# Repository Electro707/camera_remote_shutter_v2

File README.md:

# P1010 - Camera Remote Shutter Project V2
#### Rev 2

This is an open-source camera remote shutter.

This was the second revision of the [original project](https://github.com/Electro707/camera_remote_shutter), but is now treated as a seperate project due to scope creep.

Currently working on Rev 2, which is smaller and fixed some issues with V1

# Directory Structure
- `CAD`: FreeCAD enclosure and models
    - C1013: Bottom half of enclosure
    - C1014: Top half of enclosure
- `Firmware`: Firmware. Currently contains only test firmware
- `PCB`: KiCAD PCB Files
    - E1011: PCB
- `Release`: Locked in "released" files, such as Schematics, Gerbers, etc
- `SimTest`: A simulation I did in KiCAD for the trans-impedance amplifier

## Erratas
All hardware erratas and potential work-arounds are documented in [ERRATA.md](ERRATA.md)

## Firmware
WIP, currently only test firmware exists

### Setup
This project uses [stm32-cmake](https://github.com/ObKo/stm32-cmake) in the build process, so you must set it up and change the `CMAKE_TOOLCHAIN_FILE` variable in each firmware's CMAKE file. You must also download [STM32G0's MCU Package](https://github.com/STMicroelectronics/STM32CubeG0) and set the `STM32_CUBE_G0_PATH` variable to the download location.
Optionally if you have stm32cubeide installed, setup `STM32_TOOLCHAIN_PATH` in the CMAKE file, or remove it

### Compiling
To build any of the test or main applications, go into that directory and run the following:
```bash
mkdir -p build
cd build
cmake ../
make
```

### Programming
To upload the program, run the following stlink command
```bash
st-flash write <file_to_flash>.bin 0x08000000
```

Where the <file_to_flash> is the bin file inside of the build folder. `0x08000000` is the starting flash address for the STM32G0 family.

## KiCAD 3D Models
The 3D models for some components in the directory `PCB/3d_model/` are not included due to licensing reasons. You can grab the step files yourself and put it in that directory from the manufacturer. The models are
- CUI_DEVICES_SJ-2509N.step
- 615006138421_Download_STP_615006138421_rev1.stp
- c-1-1478035-0-b-3d.stp
- pec12r-4025f-n0024.stp

# License
This project is licensed under GPLv3. See [LICENSE.md](LICENSE.md) for details.

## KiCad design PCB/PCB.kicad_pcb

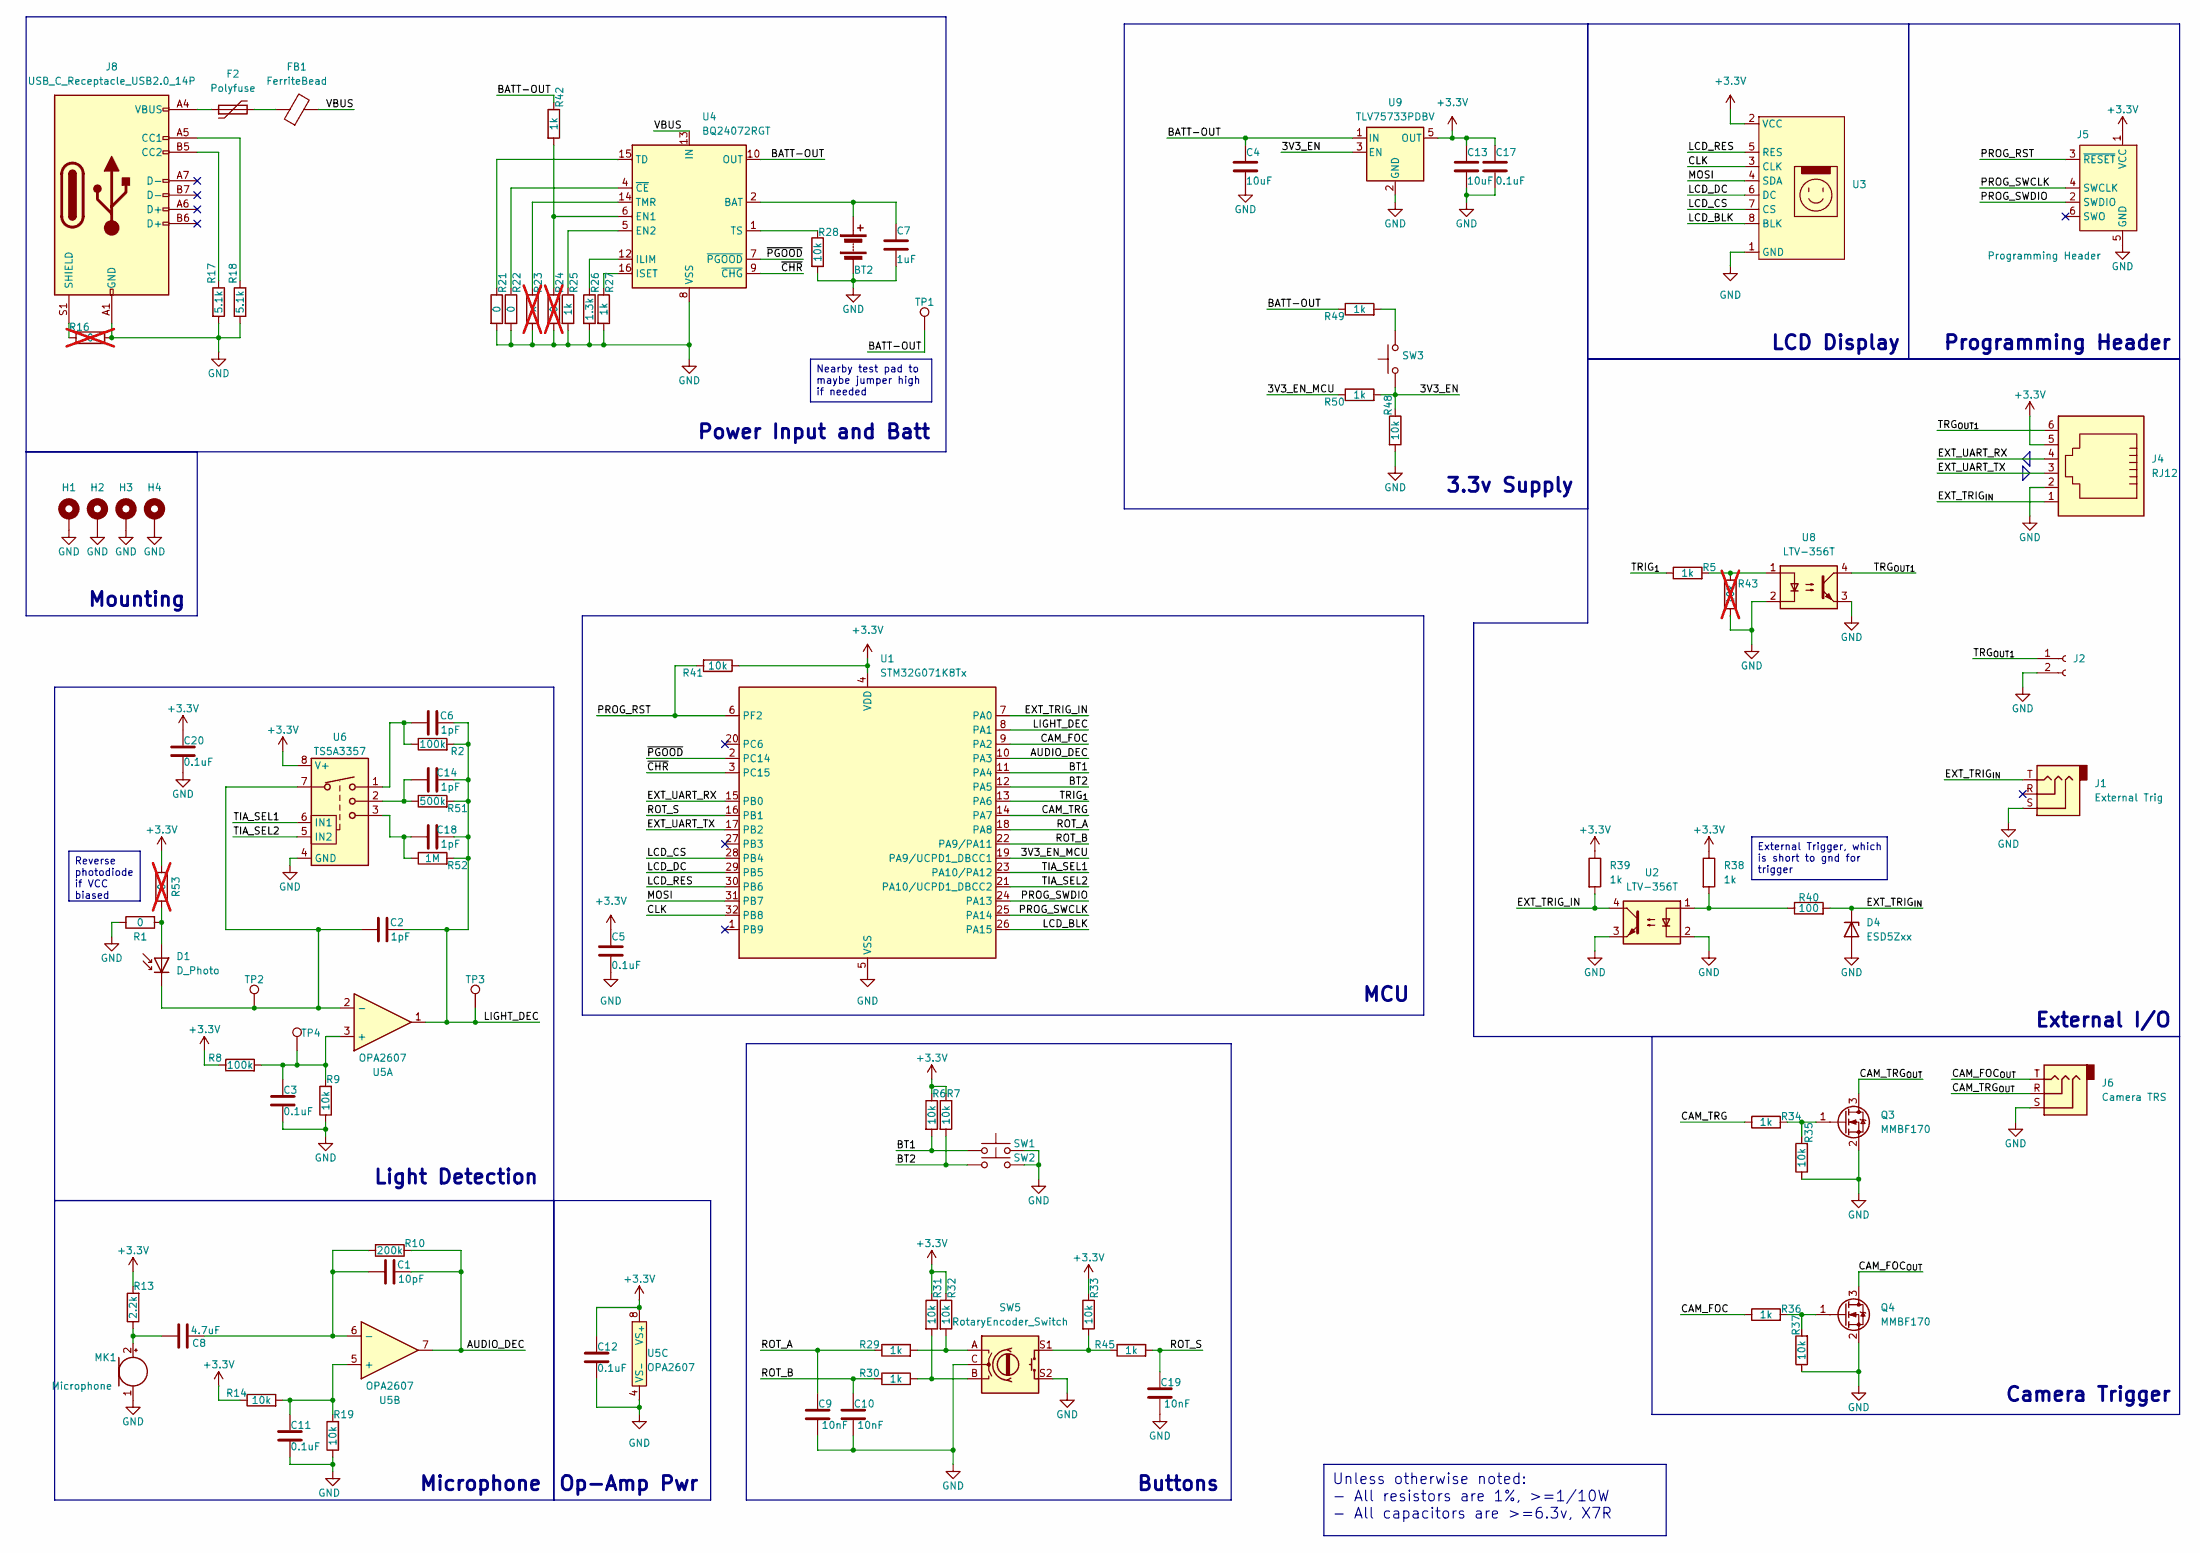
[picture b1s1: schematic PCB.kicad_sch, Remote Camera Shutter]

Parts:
BT2: Battery; JST_PH_B2B-PH-K_1x02_P2.00mm_Vertical
C1: 10pF; C_0805_2012Metric
C2, C6, C14, C18: 1pF; C_0805_2012Metric
C3, C5, C11, C12, C17, C20: 0.1uF; C_0805_2012Metric
C4, C13: 10uF; C_0805_2012Metric
C7: 1uF; C_0805_2012Metric
C8: 4.7uF; C_0805_2012Metric
C9, C10, C19: 10nF; C_0805_2012Metric
D1: D_Photo; LED_D5.0mm
D4: ESD5Zxx; D_SOD-523
F2: Polyfuse; Fuse_1210_3225Metric_Pad1.42x2.65mm_HandSolder
FB1: FerriteBead; Fuse_0805_2012Metric
H1, H2, H3, H4: MountingHole_Pad; MountingHole_3.2mm_M3_DIN965_Pad
J1: External Trig; MJ1-2503A
J2: Conn_01x02_Socket; PinHeader_1x02_P2.54mm_Vertical
J4: RJ12; RJ25_Wayconn_MJEA-660X1_Horizontal
J5: Programming Header; Tag-Connect_TC2030-IDC-NL_2x03_P1.27mm_Vertical
J6: Camera TRS; MJ1-2503A
J8: USB_C_Receptacle_USB2.0_14P; USB_C_Receptacle_GCT_USB4085
MK1: Microphone; POM-2244P-C3310-2-R
Q3, Q4: MMBF170; SOT-23
R1, R21, R22: 0; R_0805_2012Metric
R2, R8: 100k; R_0805_2012Metric
R5, R25, R27, R29, R30, R34, R36, R38, R39, R42, R45, R49, R50: 1k; R_0805_2012Metric
R6, R7, R9, R14, R19, R28, R31, R32, R33, R35, R37, R41, R48: 10k; R_0805_2012Metric
R10: 200k; R_0805_2012Metric
R13: 2.2k; R_0805_2012Metric
R16, R24, R53: 0; R_0805_2012Metric; not fitted
R17, R18: 5.1k; R_0805_2012Metric
R23: x; R_0805_2012Metric; not fitted
R26: 1.3k; R_0805_2012Metric
R40: 100; R_0805_2012Metric
R43: 10k; R_0805_2012Metric; not fitted
R51: 500k; R_0805_2012Metric
R52: 1M; R_0805_2012Metric
SW1, SW2: SW_Push; SW_PUSH_6mm
SW3: SW_Push; SW_Tactile_SPST_Angled_PTS645Vx58-2LFS
SW5: RotaryEncoder_Switch; RotaryEncoder_Bourns_Vertical_PEC12R-3x17F-Sxxxx
TP1: TestPoint; TestPoint_Pad_D1.5mm
TP2, TP3, TP4: TestPoint; TestPoint_Keystone_5005-5009_Compact
U1: STM32G071K8Tx; LQFP-32_7x7mm_P0.8mm
U2, U8: LTV-356T; SO-4_4.4x3.6mm_P2.54mm
U3: ER-TFTM1.28-1; 1.28IN LCD
U4: BQ24072RGT; VQFN-16-1EP_3x3mm_P0.5mm_EP1.6x1.6mm
U5: OPA2607; SOIC-8_3.9x4.9mm_P1.27mm
U6: TS5A3357; VSSOP-8_2.3x2mm_P0.5mm
U9: TLV75733PDBV; SOT-23-5

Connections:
+3.3V: C5.1, C12.2, C13.1, C17.1, C20.2, J4.5, J5.1 (VCC), R6.1, R7.1, R8.1, R13.2, R14.1, R31.1, R32.1, R33.1, R38.1, R39.1, R41.1, R53.2, U1.4 (VDD), U3.2 (VCC), U5.8 (VS_{+}), U6.8 (V+), U9.5 (OUT)
/3V3_EN: R48.1, R50.2, SW3.1, U9.3 (EN)
/3V3_EN_MCU: R50.1, U1.19 (PA9/UCPD1_DBCC1)
/AUDIO_DEC: C1.2, R10.1, U1.10 (PA3), U5.7
/BATT-OUT: C4.1, R42.1, R49.1, TP1.1, U4.10 (OUT), U4.11 (OUT), U9.1 (IN)
/BT1: R6.2, SW1.1, U1.11 (PA4)
/BT2: R7.2, SW2.1, U1.12 (PA5)
/CAM_FOC: R36.1, U1.9 (PA2)
/CAM_FOC_{OUT}: J6.T, Q4.3 (D)
/CAM_TRG: R34.1, U1.14 (PA7)
/CAM_TRG_{OUT}: J6.R, Q3.3 (D)
/CLK: U1.32 (PB8), U3.3 (CLK)
/EXT_TRIG_IN: R39.2, U1.7 (PA0), U2.4
/EXT_TRIG_{IN}: D4.1 (K), J1.T, J4.1, R40.2
/EXT_UART_RX: J4.4, U1.15 (PB0)
/EXT_UART_TX: J4.3, U1.17 (PB2)
/LCD_BLK: U1.26 (PA15), U3.8 (BLK)
/LCD_CS: U1.28 (PB4), U3.7 (CS)
/LCD_DC: U1.29 (PB5), U3.6 (DC)
/LCD_RES: U1.30 (PB6), U3.5 (RES)
/LIGHT_DEC: C2.2, C6.2, C14.2, C18.2, R2.2, R51.2, R52.2, TP3.1, U1.8 (PA1), U5.1
/MOSI: U1.31 (PB7), U3.4 (SDA)
/PROG_RST: J5.3 (~RESET), R41.2, U1.6 (PF2)
/PROG_SWCLK: J5.4 (SWCLK), U1.25 (PA14)
/PROG_SWDIO: J5.2 (SWDIO), U1.24 (PA13)
/ROT_A: C9.1, R29.1, U1.18 (PA8)
/ROT_B: C10.1, R30.1, U1.22 (PA9/PA11)
/ROT_S: C19.1, R45.2, U1.16 (PB1)
/TIA_SEL1: U1.23 (PA10/PA12), U6.6 (IN1)
/TIA_SEL2: U1.21 (PA10/UCPD1_DBCC2), U6.5 (IN2)
/TRG_{OUT}_{1}: J2.1, J4.6, U8.4
/TRIG_{1}: R5.1, U1.13 (PA6)
/VBUS: FB1.2, U4.13 (IN)
/~CHR: U1.3 (PC15), U4.9 (~CHG)
/~PGOOD: U1.2 (PC14), U4.7 (~PGOOD)
GND: BT2.2 (-), C3.1, C4.2, C5.2, C7.2, C9.2, C10.2, C11.1, C12.1, C13.2, C17.2, C19.2, C20.1, D4.2 (A), H1.1, H2.1, H3.1, H4.1, J1.S, J2.2, J4.2, J5.5 (GND), J6.S, J8.A1 (GND), J8.A12 (GND), J8.B1 (GND), J8.B12 (GND), MK1.1 (-), Q3.2 (S), Q4.2 (S), R1.1, R9.1, R16.2, R17.2, R18.2, R19.1, R21.2, R22.2, R23.2, R24.2, R25.2, R26.2, R27.2, R28.2, R35.1, R37.1, R43.2, R48.2, SW1.2, SW2.2, SW5.C, SW5.S2, U1.5 (VSS), U2.2, U2.3, U3.1 (GND), U4.8 (VSS), U4.17 (VSS), U5.4 (VS_{-}), U6.4 (GND), U8.2, U8.3, U9.2 (GND)
unnamed: BT2.1 (+), C7.1, U4.2 (BAT), U4.3 (BAT)
unnamed: C6.1, R2.1, U6.1
unnamed: C14.1, R51.1, U6.2
unnamed: C18.1, R52.1, U6.3
unnamed: D1.2 (A), R1.2, R53.1
unnamed: C2.1, D1.1 (K), TP2.1, U5.2 (-), U6.7
unnamed: F2.1, J8.A4 (VBUS), J8.A9 (VBUS), J8.B4 (VBUS), J8.B9 (VBUS)
unnamed: F2.2, FB1.1
unnamed: J8.A5 (CC1), R18.1
unnamed: J8.B5 (CC2), R17.1
unnamed: J8.S1 (SHIELD), R16.1
unnamed: C8.1, MK1.2 (+), R13.1
unnamed: Q3.1 (G), R34.2, R35.2
unnamed: Q4.1 (G), R36.2, R37.2
unnamed: R29.2, R32.2, SW5.A
unnamed: R30.2, R31.2, SW5.B
unnamed: R33.2, R45.1, SW5.S1
unnamed: R38.2, R40.1, U2.1
unnamed: R5.2, R43.1, U8.1
unnamed: R49.2, SW3.2
unnamed: R24.1, R42.2, U4.6 (EN1)
unnamed: R25.1, U4.5 (EN2)
unnamed: R26.1, U4.12 (ILIM)
unnamed: R27.1, U4.16 (ISET)
unnamed: R21.1, U4.15 (TD)
unnamed: R23.1, U4.14 (TMR)
unnamed: R28.1, U4.1 (TS)
unnamed: R22.1, U4.4 (~CE)
unnamed: C3.2, R8.2, R9.2, TP4.1, U5.3 (+)
unnamed: C11.2, R14.2, R19.2, U5.5 (+)
unnamed: C1.1, C8.2, R10.2, U5.6 (-)

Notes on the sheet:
External I/O
3.3v Supply
Camera Trigger
Light Detection
Op-Amp Pwr
Power Input and Batt
MCU
Microphone
Mounting
Programming Header
Buttons
LCD Display
Nearby test pad to maybe jumper high if needed
Reverse photodiode if VCC biased
External Trigger, which is short to gnd for trigger
Unless otherwise noted: - All resistors are 1%, >=1/10W - All capacitors are >=6.3v, X7R

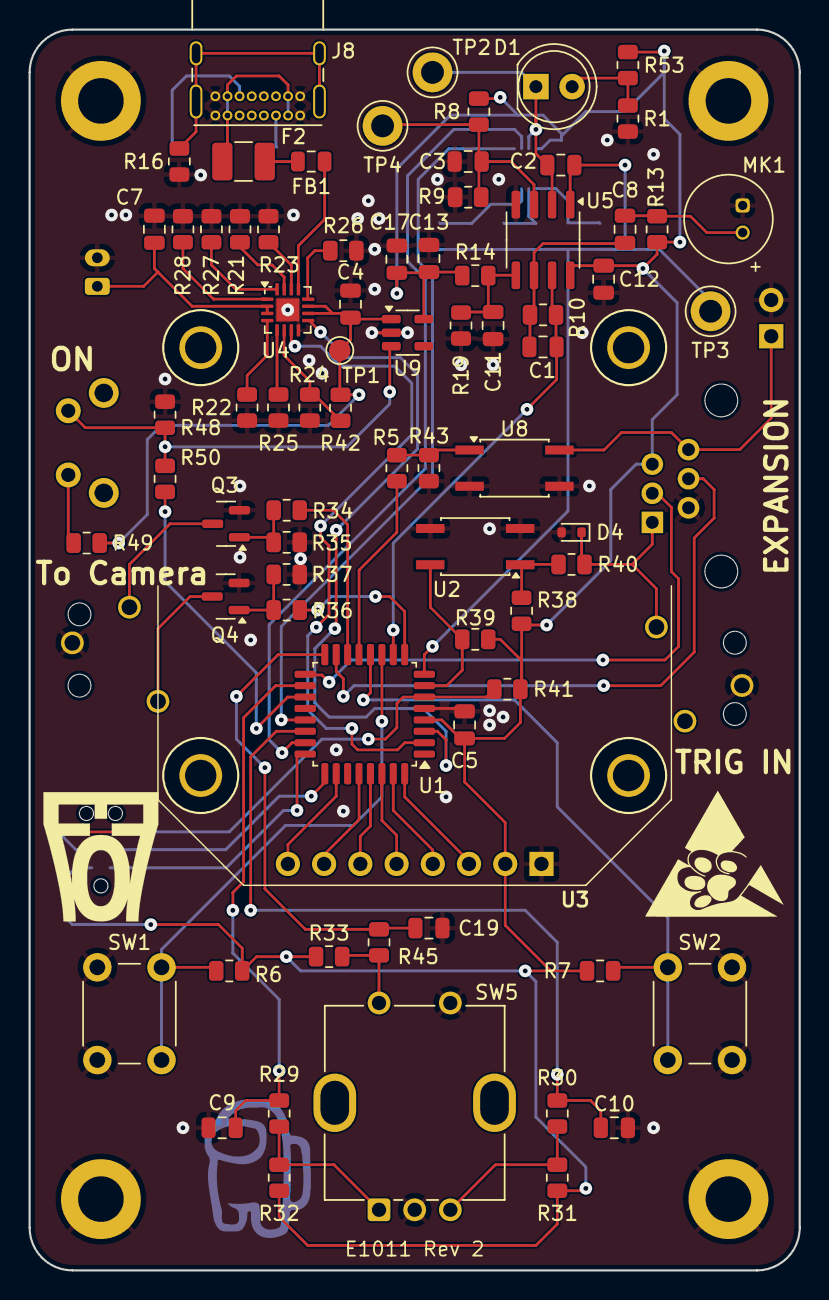
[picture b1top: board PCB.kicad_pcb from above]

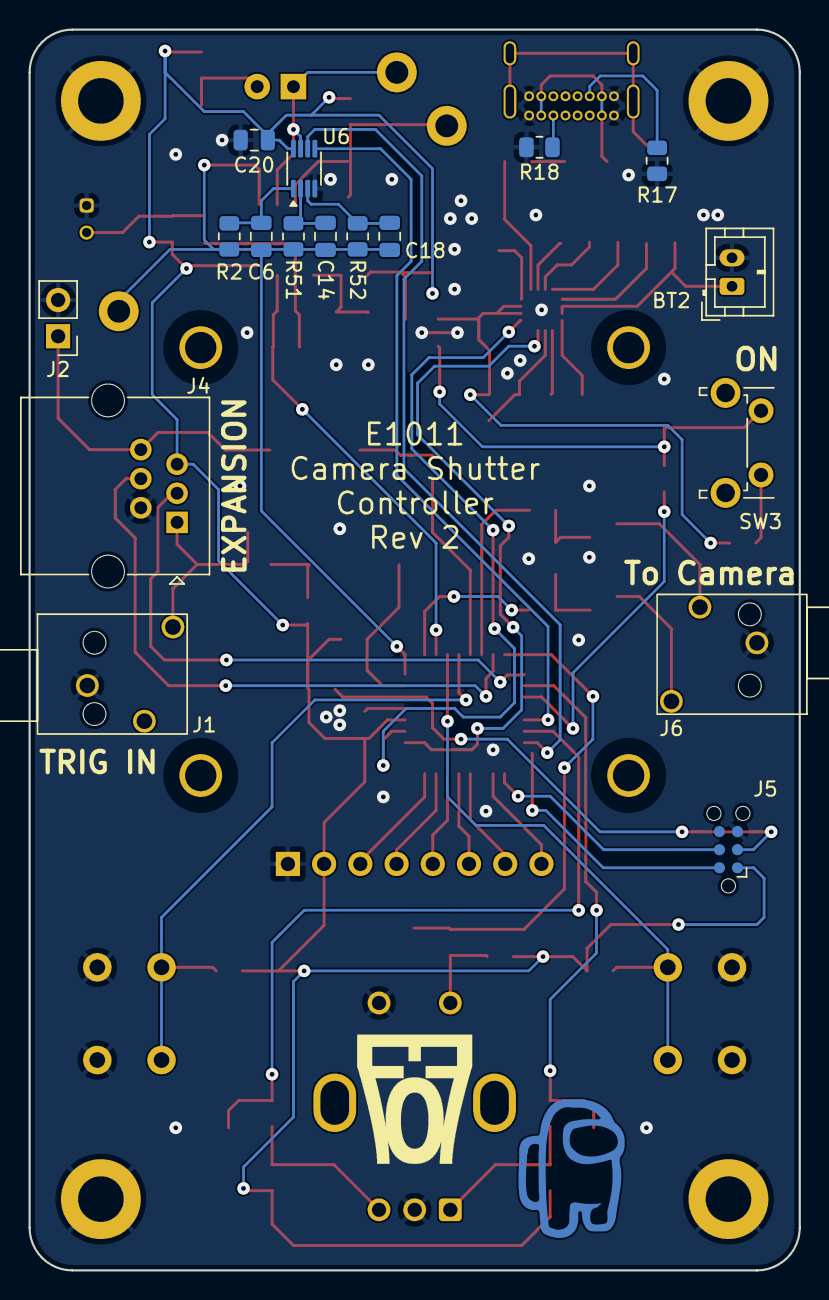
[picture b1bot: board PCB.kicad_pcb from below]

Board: 2 copper layers, 54.0 x 87.0 mm, 96 parts (17 on the bottom side), 67 nets.

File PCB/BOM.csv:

"Reference","Value","Footprint","Qty","DNP"
"BT2","Battery","Connector_JST:JST_PH_B2B-PH-K_1x02_P2.00mm_Vertical","1",""
"C1","10pF","Capacitor_SMD:C_0805_2012Metric","1",""
"C2,C6,C14,C18","1pF","Capacitor_SMD:C_0805_2012Metric","4",""
"C3,C5,C11,C12,C17,C20","0.1uF","Capacitor_SMD:C_0805_2012Metric","6",""
"C4,C13","10uF","Capacitor_SMD:C_0805_2012Metric","2",""
"C7","1uF","Capacitor_SMD:C_0805_2012Metric","1",""
"C8","4.7uF","Capacitor_SMD:C_0805_2012Metric","1",""
"C9,C10,C19","10nF","Capacitor_SMD:C_0805_2012Metric","3",""
"D1","D_Photo","LED_THT:LED_D5.0mm","1",""
"D4","ESD5Zxx","Diode_SMD:D_SOD-523","1",""
"F2","Polyfuse","Fuse:Fuse_1210_3225Metric_Pad1.42x2.65mm_HandSolder","1",""
"FB1","FerriteBead","Fuse:Fuse_0805_2012Metric","1",""
"H1,H2,H3,H4","MountingHole_Pad","MountingHole:MountingHole_3.2mm_M3_DIN965_Pad","4",""
"J1","External Trig","ProjectLibrary:MJ1-2503A","1",""
"J2","Conn_01x02_Socket","Connector_PinHeader_2.54mm:PinHeader_1x02_P2.54mm_Vertical","1",""
"J4","RJ12","Connector_RJ:RJ25_Wayconn_MJEA-660X1_Horizontal","1",""
"J6","Camera TRS","ProjectLibrary:MJ1-2503A","1",""
"J8","USB_C_Receptacle_USB2.0_14P","Connector_USB:USB_C_Receptacle_GCT_USB4085","1",""
"MK1","Microphone","Sensor_Audio:POM-2244P-C3310-2-R","1",""
"Q3,Q4","MMBF170","Package_TO_SOT_SMD:SOT-23","2",""
"R1,R21,R22","0","Resistor_SMD:R_0805_2012Metric","3",""
"R2,R8","100k","Resistor_SMD:R_0805_2012Metric","2",""
"R5,R25,R27,R29,R30,R34,R36,R38,R39,R42,R45,R49,R50","1k","Resistor_SMD:R_0805_2012Metric","13",""
"R6,R7,R9,R14,R19,R28,R31,R32,R33,R35,R37,R41,R48","10k","Resistor_SMD:R_0805_2012Metric","13",""
"R10","200k","Resistor_SMD:R_0805_2012Metric","1",""
"R13","2.2k","Resistor_SMD:R_0805_2012Metric","1",""
"R16,R24,R53","0","Resistor_SMD:R_0805_2012Metric","3","DNP"
"R17,R18","5.1k","Resistor_SMD:R_0805_2012Metric","2",""
"R23","x","Resistor_SMD:R_0805_2012Metric","1","DNP"
"R26","1.3k","Resistor_SMD:R_0805_2012Metric","1",""
"R40","100","Resistor_SMD:R_0805_2012Metric","1",""
"R43","10k","Resistor_SMD:R_0805_2012Metric","1","DNP"
"R51","500k","Resistor_SMD:R_0805_2012Metric","1",""
"R52","1M","Resistor_SMD:R_0805_2012Metric","1",""
"SW1,SW2,SW3","SW_Push","Button_Switch_THT:SW_PUSH_6mm,Button_Switch_THT:SW_Tactile_SPST_Angled_PTS645Vx58-2LFS","3",""
"SW5","RotaryEncoder_Switch","Rotary_Encoder:RotaryEncoder_Bourns_Vertical_PEC12R-3x17F-Sxxxx","1",""
"TP1,TP2,TP3,TP4","TestPoint","TestPoint:TestPoint_Keystone_5005-5009_Compact,TestPoint:TestPoint_Pad_D1.5mm","4",""
"U1","STM32G071K8Tx","Package_QFP:LQFP-32_7x7mm_P0.8mm","1",""
"U2,U8","LTV-356T","Package_SO:SO-4_4.4x3.6mm_P2.54mm","2",""
"U3","ER-TFTM1.28-1","ProjectLibrary:1.28IN LCD","1",""
"U4","BQ24072RGT","Package_DFN_QFN:VQFN-16-1EP_3x3mm_P0.5mm_EP1.6x1.6mm","1",""
"U5","OPA2607","Package_SO:SOIC-8_3.9x4.9mm_P1.27mm","1",""
"U6","TS5A3357","Package_SO:VSSOP-8_2.3x2mm_P0.5mm","1",""
"U9","TLV75733PDBV","Package_TO_SOT_SMD:SOT-23-5","1",""

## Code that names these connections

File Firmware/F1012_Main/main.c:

#include "stm32g0xx.h"
#include "stm32g0xx_ll_rcc.h"
#include "stm32g0xx_ll_system.h"
#include "stm32g0xx_ll_utils.h"
#include "gc9a01.h"
#include "config.h"
#include <stddef.h>
#include <stdlib.h>
#include <string.h>
#include "nanoprintf.h"

void autoShutdownService(void);
void shutdownDevice(void);
void selectTiaSens(uint8_t sens);
void line_draw_abstract(uint8_t *canvasBuff, uint16_t canvasW, uint16_t x0, uint16_t y0, uint16_t x1, uint16_t y1);
void line_draw_vert_abstract(uint8_t *canvasBuff, uint16_t canvasW, uint16_t x, uint16_t h);

// run-time modes
typedef enum{
	STATE_RESET,		// reset state
	STATE_STANDBY,		// standby, not doing anything with pictures
	STATE_EDITING_VAR,	// editing variable in UI
	STATE_ARMED,		// armed, waiting to take picture
	STATE_TRIG,			// camera triggered
	STATE_SHUTDOWN		// shutdown
}stateMachine_e;

// to keep track of what we are editing through UI
typedef enum{
	UI_EDIT_SHUTTER_TIME,
	UI_EDIT_TRIG_TIME,
	UI_EDIT_TIMELAPSE_N,
	UI_EDIT_TIMELAPSE_DUR,
}uiEditMode_e;

stateMachine_e state;
uint autoShutdownTimer;		// counter for auto shutting down
uint lastEncoderState;
uint lastLcdUpdate;			// last time since we updated the lcd
bool trigUpdateLcd;

void initMcu(void){
	// init clock, 32Mhz system and periferal clock
	LL_FLASH_SetLatency(LL_FLASH_LATENCY_1);
	while(LL_FLASH_GetLatency() != LL_FLASH_LATENCY_1);

	LL_RCC_HSI_Enable();
	while(LL_RCC_HSI_IsReady() != 1);

	LL_RCC_PLL_ConfigDomain_SYS(LL_RCC_PLLSOURCE_HSI, LL_RCC_PLLM_DIV_1, 8, LL_RCC_PLLR_DIV_2);
	LL_RCC_PLL_Enable();
	LL_RCC_PLL_EnableDomain_SYS();
	while(LL_RCC_PLL_IsReady() != 1);

	LL_RCC_SetAHBPrescaler(LL_RCC_SYSCLK_DIV_1);
	LL_RCC_SetSysClkSource(LL_RCC_SYS_CLKSOURCE_PLL);
	while(LL_RCC_GetSysClkSource() != LL_RCC_SYS_CLKSOURCE_STATUS_PLL);

	LL_RCC_SetAPB1Prescaler(LL_RCC_APB1_DIV_1);
	LL_Init1msTick(64000000);
	LL_SetSystemCoreClock(64000000);

	// remap PA11 to PA9
	RCC->APBENR2 |= RCC_APBENR2_SYSCFGEN;
	SYSCFG->CFGR1 |= SYSCFG_CFGR1_UCPD2_STROBE | SYSCFG_CFGR1_UCPD1_STROBE;
	// SYSCFG->CFGR1 |= SYSCFG_CFGR1_PA11_RMP;

	// init gpio
	// enable clock for port a, b, and c
	RCC->IOPENR |= RCC_IOPENR_GPIOAEN | RCC_IOPENR_GPIOBEN | RCC_IOPENR_GPIOCEN;

	// PA6 (Trig_1) - output
	// PA7 (CAM_TRIG) - output
	// PA8 (ROT_A) - alternate
	// PA9 (ROT_B, fixed through pcb mod) - alternate
	// PA10 (TIA_SEL2) - output
	// PA11 (3V3_EN_MCU, fixed through pcb mod) - output
	// PA12 (TIA_SEL1) - output
	// PA13 (SWDIO) - alternate
	// PA14 (SWCLK) - alternate
	// PA15 (LCB_BLK) - output
	GPIOA->MODER = 0x695a5fff;
	GPIOA->AFR[1] |= 0x22;              // A8 and A9 -> AF2 (Timer 1 inputs)

	// port b output
	// PB4 (LCD_CS) -> output
	// PB5 (LCD_DC) -> output
	// PB6 (LCD_RES) -> output
	// PB7 (MOSI) -> alternate function
	// PB8 (MISO) -> alternate function
	GPIOB->MODER = 0xFFFE95FF;
	GPIOB->OSPEEDR = 0x0003EA00;        // all high speed for B4 to B6, very high speed for B7-B8
	GPIOB->AFR[0] |= 0x01 << 28;        // B7 -> AF1
	GPIOB->AFR[1] |= 0x01 << 0;         // B8 -> AF1

	// bring all output to reset state
	GPIOA->ODR = 0x800; // pa11
	GPIOB->ODR = 0;
	GPIOC->ODR = 0;

	// init spi, clk/2 (32Mhz), master
	RCC->APBENR1 |= RCC_APBENR1_SPI2EN;
	SPI2->CR2 = 0x0700;
	SPI2->CR1 = 0x0304;

	// init adc
	RCC->APBENR2 |= RCC_APBENR2_ADCEN;
	// Disable ADC in case it was beforehand
	if(ADC1->CR & ADC_CR_ADEN){
		ADC1->CR |= ADC_CR_ADDIS;
		while(ADC1->CR & ADC_CR_ADDIS);
	}

	ADC1->CFGR2 = 0x40000000;       // PCLK/2
	ADC1->SMPR = (0b11 << ADC_SMPR_SMP1_Pos);   // 12.5 ADC clock cycles for sampling time
	ADC1->CHSELR = 1 << 1;          // light as input
	// ADC1->CHSELR = 1 << 3;          // mic as input
	ADC1->CR = ADC_CR_ADVREGEN;      // ADVREGEN=1

	// init timer 1 in quatrature input mode (pa8-ch1 and pa9-ch2)
	RCC->APBENR2 |= RCC_APBENR2_TIM1EN;
	TIM1->SMCR = 0x0003;        // encoder mode 3 (up and down)
	TIM1->CCER = 0x22;      // falling edge
	TIM1->CCMR1 = (0b0110 << TIM_CCMR1_IC1F_Pos) | (0b0110 << TIM_CCMR1_IC1F_Pos) | TIM_CCMR1_CC1S_1 | TIM_CCMR1_CC2S_1;
	TIM1->CR2 = 0x0;
	TIM1->CR1 = 0x1;

	// init timer 14 as the real time interrupt of 1mS
	RCC->APBENR2 |= RCC_APBENR2_TIM14EN;
	TIM14->PSC = 512;
	TIM14->ARR = 125;
	TIM14->CNT = 0;
	TIM14->CR1 = TIM_CR1_URS;
	TIM14->DIER = TIM_DIER_UIE;

	// init timer 6 as a longer timer, period of 10 seconds
	RCC->APBENR1 |= RCC_APBENR1_TIM6EN;
	TIM6->CR1 = TIM_CR1_URS;
	TIM6->DIER = TIM_DIER_UIE;
	TIM6->PSC = 40000;
	TIM6->ARR = 16000;
	TIM6->CNT = 0;

	// set led backlight on
	GPIOA->ODR |= 1 << 15;
	DISP_CS_1;

	NVIC_EnableIRQ(TIM6_DAC_LPTIM1_IRQn);
	NVIC_EnableIRQ(TIM14_IRQn);

	SPI2->CR1 |= SPI_CR1_SPE;
}

void adcCal(void){
	unsigned int cal = 0;
	uint8_t n = 8;
	while(n--){
		ADC1->CR |= ADC_CR_ADCAL;
		while(ADC1->CR & ADC_CR_ADCAL);
		cal += ADC1->CALFACT + 1;
	}
	cal >>= 3;
	ADC1->CALFACT = cal;
}

void initSetupScreen(void){
	uint y = 50;
	gc9a01_fill_screen(gc9a01_color_black);

	gc9a01_print_text_sma("Shutter Time:", 50, y, gc9a01_color_black, gc9a01_color_white, ALIGN_LEFT, NULL);
	y += 16;
	
	gc9a01_print_text_sma("Time To Trig:", 50, y, gc9a01_color_white, gc9a01_color_black, ALIGN_LEFT, NULL);
	y += 16;

	gc9a01_print_text_sma("Timelapse: ", 50, y, gc9a01_color_white, gc9a01_color_black, ALIGN_LEFT, NULL);
	y += 16;

	gc9a01_print_text_sma("N Pics: ", 50, y, gc9a01_color_white, gc9a01_color_black, ALIGN_LEFT, NULL);
	y += 16;

	gc9a01_print_text_sma("Interval: ", 50, y, gc9a01_color_white, gc9a01_color_black, ALIGN_LEFT, NULL);
	y += 16;
}

int main(void)
{
	char nStr[10];

	initMcu();
	autoShutdownTimer = 0;
	lastLcdUpdate = 1000;		// technically infinite
	trigUpdateLcd = false;

	selectTiaSens(0);


	gc9a01_init();


	initSetupScreen();

	TIM1->CNT = 100;
	lastEncoderState = 100;

	TIM14->CR1 |= TIM_CR1_CEN;		// enable timer
	TIM6->CR1 |= TIM_CR1_CEN;		// enable timer
	__enable_irq();

	for(EVER){
		// todo: trigger if encoder is rotated or button pressed to reset auto shutdown timer
		if(trigUpdateLcd){
			if(lastEncoderState != TIM1->CNT){
				lastEncoderState = TIM1->CNT;
				npf_snprintf(nStr, 5, "%04u", (uint)TIM1->CNT);
        		gc9a01_print_text_sma(nStr, 162, 50, 0xFFFF, 0, ALIGN_LEFT, NULL);
				trigUpdateLcd = true;
			}
		}
	}
	return 0;
}

/*
 * real time interrupt triggered by TIMx
 * this runs every 1Khz
 */
void TIM14_IRQHandler(void){
	TIM14->SR = 0;		// clear pending interrupt

	if(trigUpdateLcd == false){
		if(lastLcdUpdate >= 100){
			trigUpdateLcd = true;
		}else{
			lastLcdUpdate++;
		}
	}
}

// called once every 10 seconds
void TIM6_DAC_LPTIM1_IRQHandler(void){
	TIM6->SR = 0;	// clear pending interrupt
	
	autoShutdownTimer += 1;
	if(autoShutdownTimer > AUTO_SHUTDOWN_INTERVAL){
		shutdownDevice();
	}
}

// service to clear the auto-shutdown timer
void autoShutdownService(void){
	autoShutdownTimer = 0;
}

void shutdownDevice(void){
	GPIOA->BRR = 1 << PIN_PSU_ENABLE;
}

/**
 * Selects the amplification amount from the TransImpedance Amplifier circuit
 * Range 0 (disabled) to 3 (max amp)
 */
void selectTiaSens(uint8_t sens){
	switch(sens){
		case 0:
			GPIOA->BRR = (1 << PIN_TIA_SEL_1);          // clear
			GPIOA->BRR = (1 << PIN_TIA_SEL_2);          // clear
			break;
		case 1:
			GPIOA->BSRR = (1 << PIN_TIA_SEL_1);         // set
			GPIOA->BSRR = (1 << PIN_TIA_SEL_2*2);       // clear
			break;
		case 2:
			GPIOA->BSRR = (1 << PIN_TIA_SEL_1*2);       // clear
			GPIOA->BSRR = (1 << PIN_TIA_SEL_2);         // set
			break;
		case 3:
			GPIOA->BSRR = (1 << PIN_TIA_SEL_1);         // set
			GPIOA->BSRR = (1 << PIN_TIA_SEL_2);         // set
			break;
		default:
			// todo: error handling
			break;
	}
}

void line_draw_vert_abstract(uint8_t *canvasBuff, uint16_t canvasW, uint16_t x, uint16_t h){
	int16_t canvasIdx;

	for(int y=0;y<h;y++){
		canvasIdx = (y*canvasW) + x / 8;
		canvasBuff[canvasIdx] |= 1 << (x & 0b111);
	}
}

/**
 * draws a canvas
 * buffer is [Y][X/8], and is bit filled
 */
void line_draw_abstract(uint8_t *canvasBuff, uint16_t canvasW, uint16_t x0, uint16_t y0, uint16_t x1, uint16_t y1){
	// https://en.wikipedia.org/wiki/Bresenham's_line_algorithm#All_cases
	int16_t dx = abs(x1-x0);
	int16_t dy = -abs(y1-y0);
	int16_t sx = x0 < x1 ? 1 : -1;
	int16_t sy = y0 < y1 ? 1 : -1;
	int16_t error = dx + dy;

	int16_t canvasIdx;

    while(1){
        canvasIdx = (y0*canvasW) + x0 / 8;
        if(canvasIdx < 0){
            canvasIdx = 0;
        }
        canvasBuff[canvasIdx] |= 1 << (x0 & 0b111);

		if((2*error) >= dy){
			if(x0 == x1){break;}
			error += dy;
			x0 += sx;
		}
		if((2*error) <= dx){
			if(y0 == y1){break;}
			error += dx;
			y0 += sy;
		}

	}
}

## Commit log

2025-01-19 Initial commit, files push
2025-08-16 Updated project name to correct one
2025-08-16 Clarified project in readme
2025-08-24 Rev 2 of the PCB with modified test firmware and enclosure
2025-08-24 Finished first rev of top enclosure
2025-08-24 Moved and renamed stuff. Expanded on README. Broke out hardware issues into ERRATA.md
2025-08-26 Added vscode files. Started work on main firmware
